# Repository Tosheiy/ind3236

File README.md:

# ind3236（自作キーボード）
右手３２キー、左手３６キーの分離型キーボードです。
基盤＋簡易ケース（サンドイッチ型）

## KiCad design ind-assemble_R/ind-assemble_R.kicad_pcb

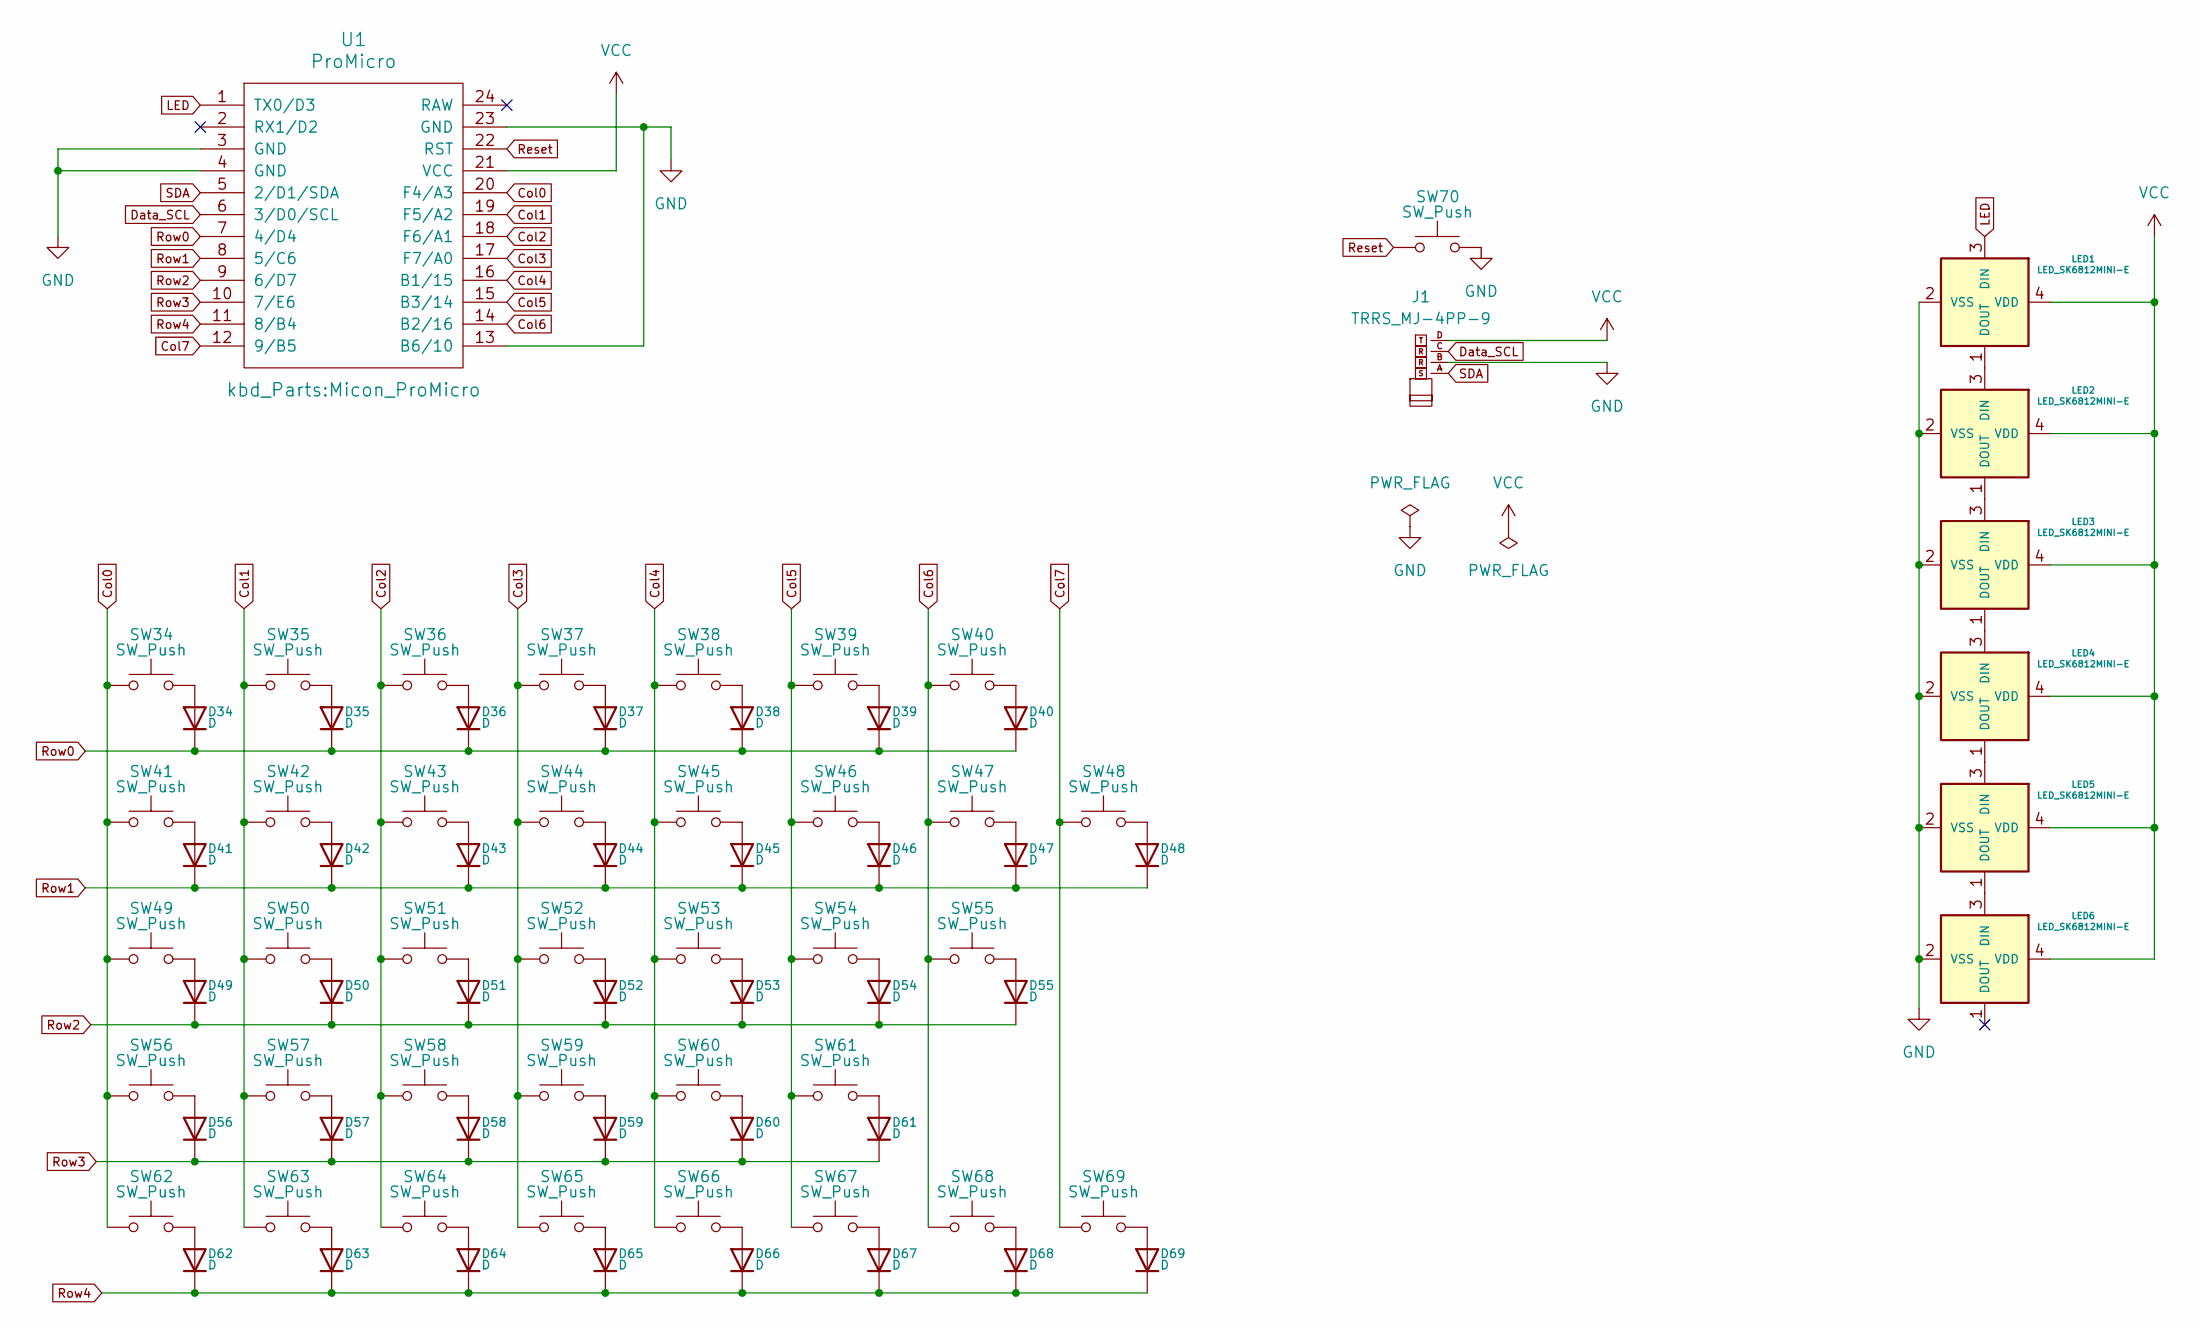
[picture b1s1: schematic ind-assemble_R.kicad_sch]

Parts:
D34, D35, D36, D37, D38, D39, D40, D41, D42, D43, D44, D45, D46, D47, D48, D49, D50, D51, D52, D53, D54, D55, D56, D57, D58, D59, D60, D61, D62, D63, D64, D65, D66, D67, D68, D69: D; Diode_TH_SMD
J1: TRRS_MJ-4PP-9
LED1, LED2, LED3, LED4, LED5, LED6: LED_SK6812MINI-E; LED_SK6812MINI-E_BL
SW34, SW35, SW36, SW37, SW38, SW39, SW41, SW42, SW43, SW44, SW45, SW46, SW47, SW49, SW50, SW51, SW52, SW53, SW54, SW56, SW57, SW58, SW59, SW60, SW62, SW63: SW_Push; CherryMX_Hotswap_1u
SW40: SW_Push; CherryMX_Hotswap_2u
SW48: SW_Push; CherryMX_Hotswap_1.5u
SW55: SW_Push; CherryMX_Hotswap_2.25u
SW61: SW_Push; CherryMX_Hotswap_2.75u
SW64, SW65, SW66, SW67, SW68, SW69: SW_Push; CherryMX_Hotswap_1.25u
SW70: SW_Push; ResetSW
U1: ProMicro; Micon_ProMicro

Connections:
Col0: SW34.1, SW41.1, SW49.1, SW56.1, SW62.1, U1.20 (F4/A3)
Col1: SW35.1, SW42.1, SW50.1, SW57.1, SW63.1, U1.19 (F5/A2)
Col2: SW36.1, SW43.1, SW51.1, SW58.1, SW64.1, U1.18 (F6/A1)
Col3: SW37.1, SW44.1, SW52.1, SW59.1, SW65.1, U1.17 (F7/A0)
Col4: SW38.1, SW45.1, SW53.1, SW60.1, SW66.1, U1.16 (B1/15)
Col5: SW39.1, SW46.1, SW54.1, SW61.1, SW67.1, U1.15 (B3/14)
Col6: SW40.1, SW47.1, SW55.1, SW68.1, U1.14 (B2/16)
Col7: SW48.1, SW69.1, U1.12 (9/B5)
Data_SCL: J1.C, U1.6 (3/D0/SCL)
GND: J1.B, LED1.2 (VSS), LED2.2 (VSS), LED3.2 (VSS), LED4.2 (VSS), LED5.2 (VSS), LED6.2 (VSS), SW70.2, U1.3 (GND), U1.4 (GND), U1.13 (B6/10), U1.23 (GND)
LED: LED1.3 (DIN), U1.1 (TX0/D3)
unnamed: D34.2 (A), SW34.2
unnamed: D35.2 (A), SW35.2
unnamed: D36.2 (A), SW36.2
unnamed: D37.2 (A), SW37.2
unnamed: D38.2 (A), SW38.2
unnamed: D39.2 (A), SW39.2
unnamed: D40.2 (A), SW40.2
unnamed: D41.2 (A), SW41.2
unnamed: D42.2 (A), SW42.2
unnamed: D43.2 (A), SW43.2
unnamed: D44.2 (A), SW44.2
unnamed: D45.2 (A), SW45.2
unnamed: D46.2 (A), SW46.2
unnamed: D47.2 (A), SW47.2
unnamed: D48.2 (A), SW48.2
unnamed: D49.2 (A), SW49.2
unnamed: D50.2 (A), SW50.2
unnamed: D51.2 (A), SW51.2
unnamed: D52.2 (A), SW52.2
unnamed: D53.2 (A), SW53.2
unnamed: D54.2 (A), SW54.2
unnamed: D55.2 (A), SW55.2
unnamed: D56.2 (A), SW56.2
unnamed: D57.2 (A), SW57.2
unnamed: D58.2 (A), SW58.2
unnamed: D59.2 (A), SW59.2
unnamed: D60.2 (A), SW60.2
unnamed: D61.2 (A), SW61.2
unnamed: D62.2 (A), SW62.2
unnamed: D63.2 (A), SW63.2
unnamed: D64.2 (A), SW64.2
unnamed: D65.2 (A), SW65.2
unnamed: D66.2 (A), SW66.2
unnamed: D67.2 (A), SW67.2
unnamed: D68.2 (A), SW68.2
unnamed: D69.2 (A), SW69.2
unnamed: LED1.1 (DOUT), LED2.3 (DIN)
unnamed: LED2.1 (DOUT), LED3.3 (DIN)
unnamed: LED3.1 (DOUT), LED4.3 (DIN)
unnamed: LED4.1 (DOUT), LED5.3 (DIN)
unnamed: LED5.1 (DOUT), LED6.3 (DIN)
Reset: SW70.1, U1.22 (RST)
Row0: D34.1 (K), D35.1 (K), D36.1 (K), D37.1 (K), D38.1 (K), D39.1 (K), D40.1 (K), U1.7 (4/D4)
Row1: D41.1 (K), D42.1 (K), D43.1 (K), D44.1 (K), D45.1 (K), D46.1 (K), D47.1 (K), D48.1 (K), U1.8 (5/C6)
Row2: D49.1 (K), D50.1 (K), D51.1 (K), D52.1 (K), D53.1 (K), D54.1 (K), D55.1 (K), U1.9 (6/D7)
Row3: D56.1 (K), D57.1 (K), D58.1 (K), D59.1 (K), D60.1 (K), D61.1 (K), U1.10 (7/E6)
Row4: D62.1 (K), D63.1 (K), D64.1 (K), D65.1 (K), D66.1 (K), D67.1 (K), D68.1 (K), D69.1 (K), U1.11 (8/B4)
SDA: J1.A, U1.5 (2/D1/SDA)
VCC: J1.D, LED1.4 (VDD), LED2.4 (VDD), LED3.4 (VDD), LED4.4 (VDD), LED5.4 (VDD), LED6.4 (VDD), U1.21 (VCC)

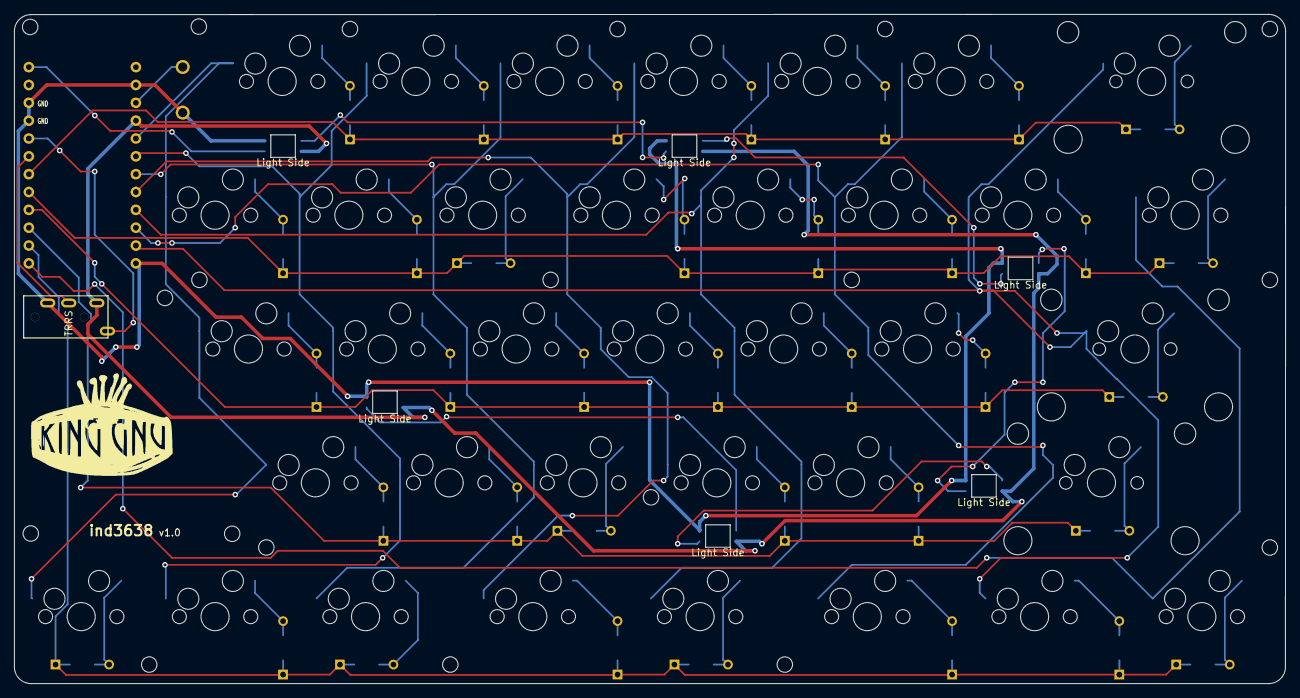
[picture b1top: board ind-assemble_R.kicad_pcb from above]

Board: 2 copper layers, 181.0 x 95.3 mm, 100 parts (1 on the bottom side), 60 nets.

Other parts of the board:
Ref**: Val**; m2_Screw_Hole
Ref**#2, Ref**#3, Ref**#4, Ref**#5, Ref**#6, Ref**#7, Ref**#8, Ref**#9, Ref**#10, Ref**#11, Ref**#12, Ref**#13, Ref**#14, Ref**#15, Ref**#16, Ref**#17, Ref**#18, Ref**#19: Val**; m2_Screw_Hole

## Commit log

2023-10-04 makingPCB
2024-04-01 complete_ind3236v1
